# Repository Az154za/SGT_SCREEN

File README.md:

# SGT_SCREEN
Well this is a DEV BOARD that has 12*12 led screen ( matrix) driven by led DRIVER IS31FL3737 and controlled by RP2040
# SCHEMATIC

# PCB

# 3D preview 

# BOM
| # | Component | Supplier | Qty | Unit Price | Total (USD) |
|---|-----------|----------|-----|------------|-------------|
| 1 | PCB | JLCPCB | 2 | $81 | $81 |
| | | | | **TOTAL** | **$81** |

I hope you like this project

This project is sponsored by @JLCPCB

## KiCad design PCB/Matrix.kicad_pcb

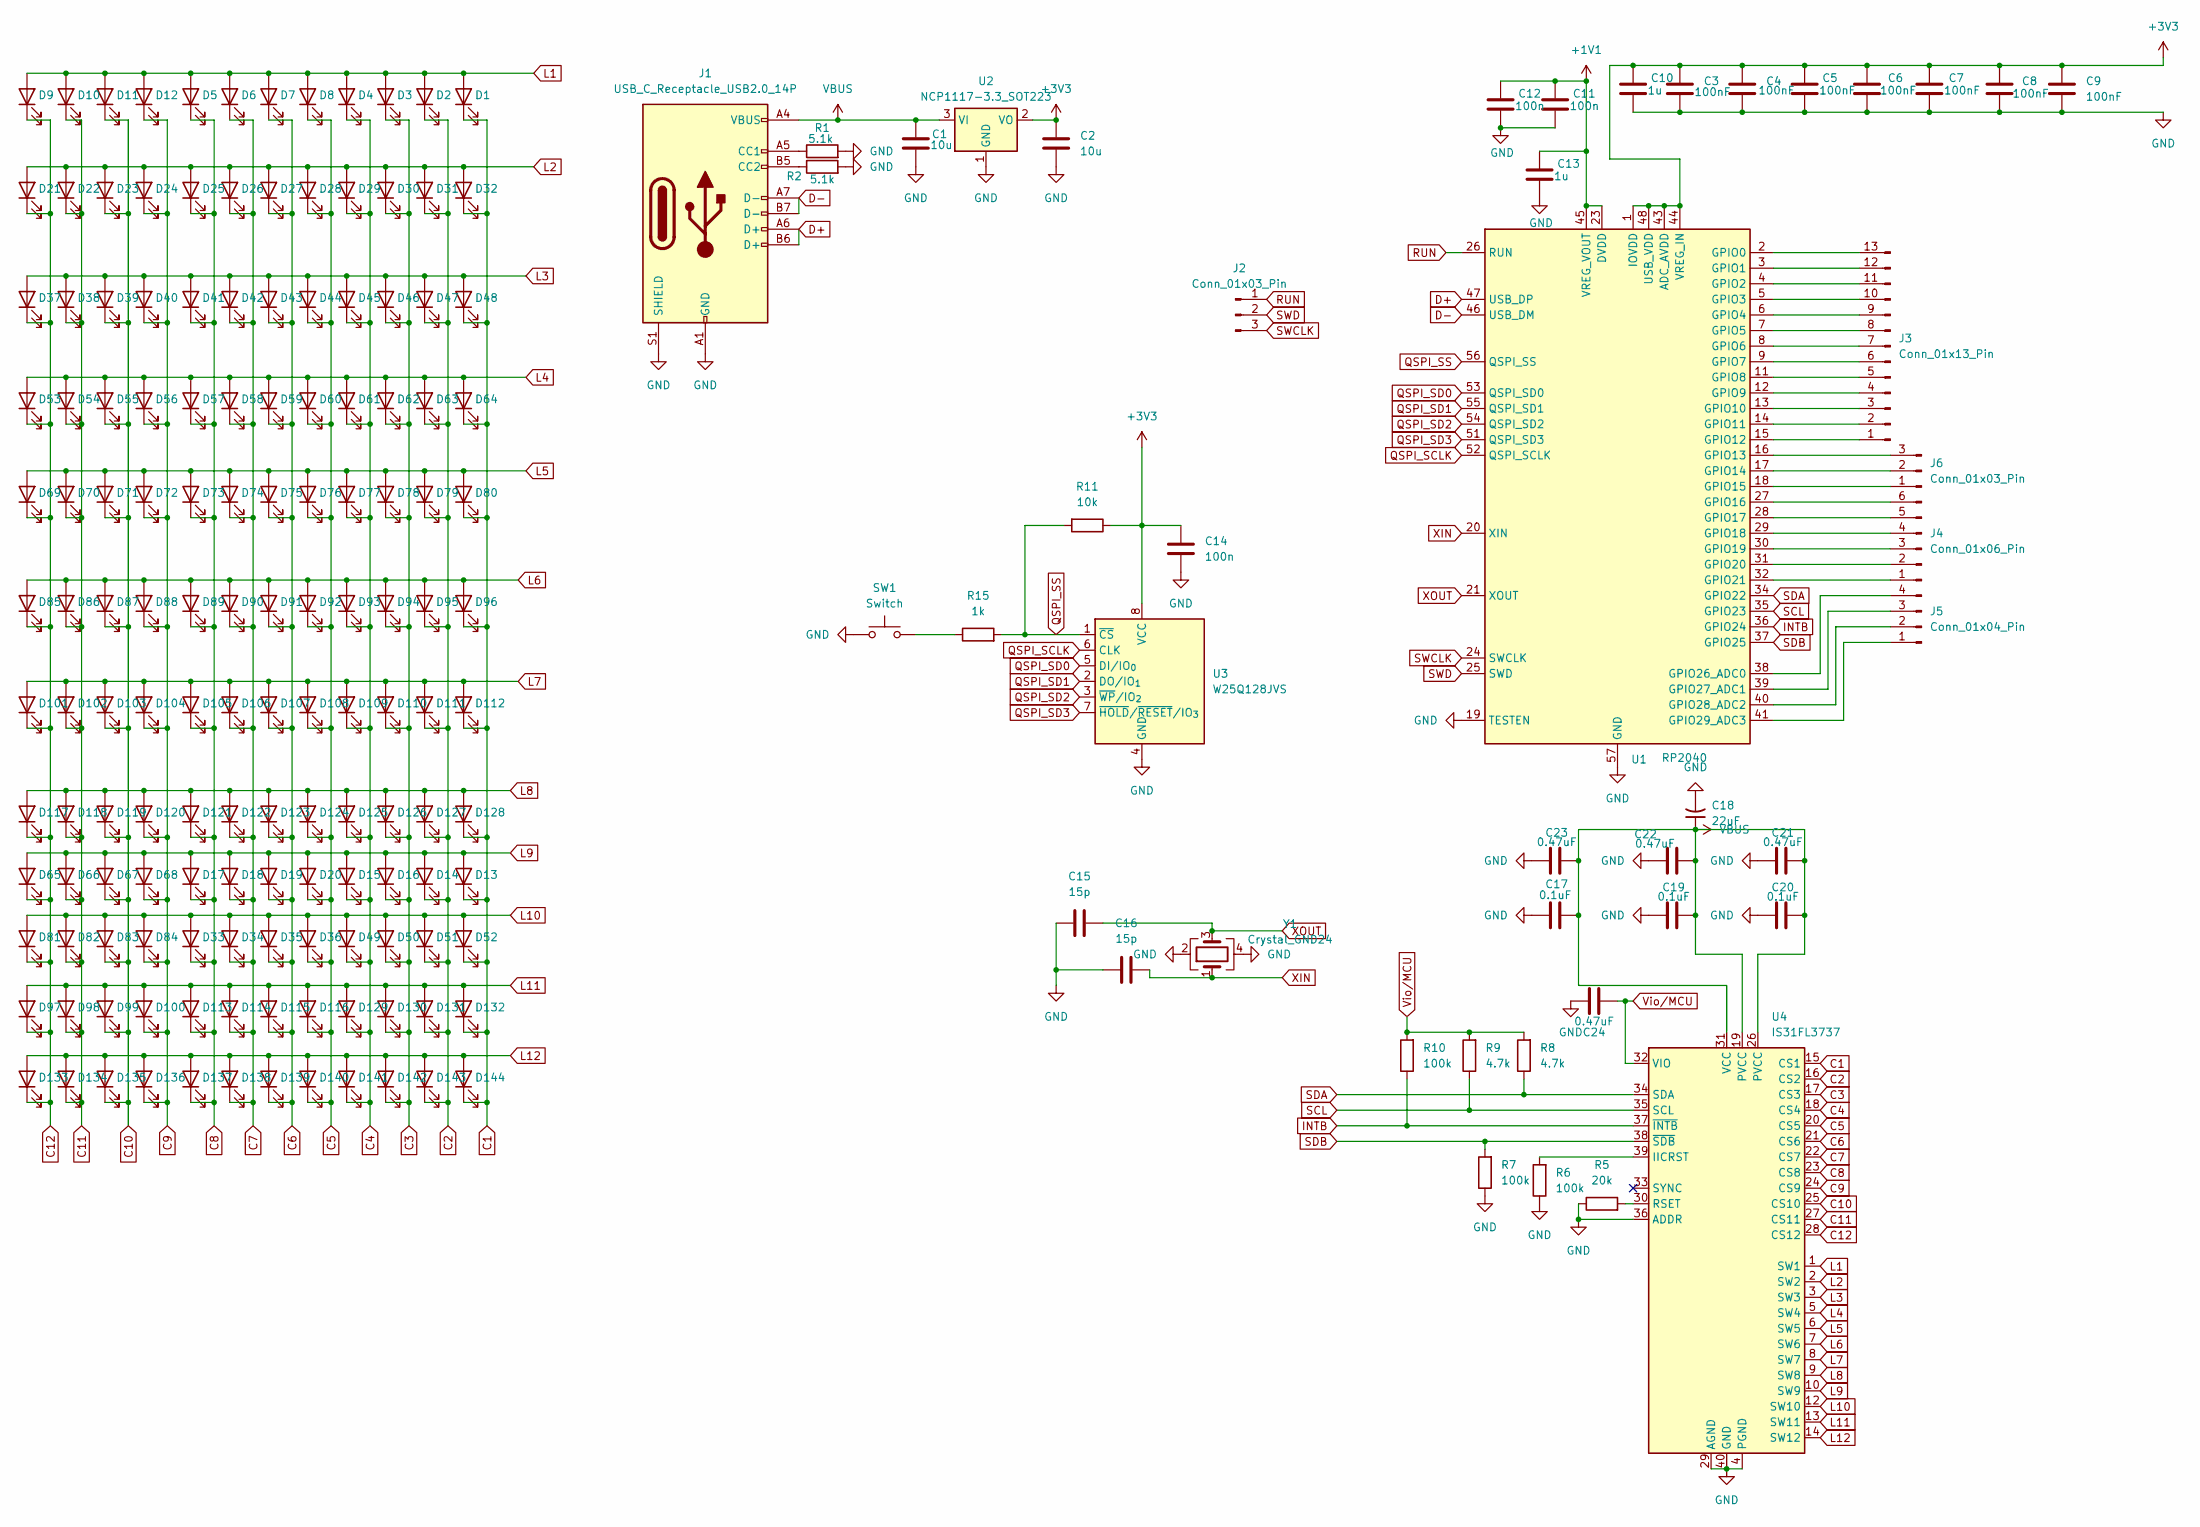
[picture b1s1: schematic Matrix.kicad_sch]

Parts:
C1, C2: 10u; C_0603_1608Metric
C3, C4, C5, C6, C7, C8, C9: 100nF; C_0402_1005Metric
C10, C13: 1u; C_0402_1005Metric
C11, C12, C14: 100n; C_0402_1005Metric
C15, C16: 15p; C_0402_1005Metric
C17, C19, C20: 0.1uF; C_0402_1005Metric
C18: 22uF; C_0402_1005Metric
C21, C22, C23, C24: 0.47uF; C_0402_1005Metric
D1, D2, D3, D4, D5, D6, D7, D8, D9, D10, D11, D12, D13, D14, D15, D16, D17, D18, D19, D20, D21, D22, D23, D24, D25, D26, D27, D28, D29, D30, D31, D32, D33, D34, D35, D36, D37, D38, D39, D40, D41, D42, D43, D44, D45, D46, D47, D48, D49, D50, D51, D52, D53, D54, D55, D56, D57, D58, D59, D60, D61, D62, D63, D64, D65, D66, D67, D68, D69, D70, D71, D72, D73, D74, D75, D76, D77, D78, D79, D80, D81, D82, D83, D84, D85, D86, D87, D88, D89, D90, D91, D92, D93, D94, D95, D96, D97, D98, D99, D100, D101, D102, D103, D104, D105, D106, D107, D108, D109, D110, D111, D112, D113, D114, D115, D116, D117, D118, D119, D120, D121, D122, D123, D124, D125, D126, D127, D128, D129, D130, D131, D132, D133, D134, D135, D136, D137, D138, D139, D140, D141, D142, D143, D144: LED; LED_0402_1005Metric
J1: USB_C_Receptacle_USB2.0_14P; USB_C_Receptacle_HRO_TYPE-C-31-M-12
J2: Conn_01x03_Pin; PinSocket_1x03_P2.54mm_Vertical
J3: Conn_01x13_Pin; PinHeader_1x13_P1.00mm_Vertical_SMD_Pin1Left
J4: Conn_01x06_Pin; PinHeader_1x06_P1.00mm_Vertical_SMD_Pin1Left
J5: Conn_01x04_Pin; PinHeader_1x04_P1.00mm_Vertical_SMD_Pin1Left
J6: Conn_01x03_Pin; PinHeader_1x03_P1.00mm_Vertical_SMD_Pin1Left
R1, R2: 5.1k; R_0402_1005Metric
R5: 20k; R_0402_1005Metric
R6, R7, R10: 100k; R_0402_1005Metric
R8, R9: 4.7k; R_0402_1005Metric
R11: 10k; R_0402_1005Metric
R15: 1k; R_0402_1005Metric
SW1: Switch; SW_SPST_SKQG_WithoutStem
U1: RP2040; QFN-56-1EP_7x7mm_P0.4mm_EP3.2x3.2mm
U2: NCP1117-3.3_SOT223; SOT-223-3_TabPin2
U3: W25Q128JVS; SOIC-8_5.3x5.3mm_P1.27mm
U4: IS31FL3737; QFN-40-1EP_5x5mm_P0.4mm_EP3.8x3.8mm
Y1: Crystal_GND24; Crystal_SMD_3225-4Pin_3.2x2.5mm

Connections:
+1V1: C11.1, C12.1, C13.1, U1.23 (DVDD), U1.45 (VREG_VOUT), U1.50 (DVDD)
+3V3: C2.1, C3.1, C4.1, C5.1, C6.1, C7.1, C8.1, C9.1, C10.1, C14.1, R11.1, U1.1 (IOVDD), U1.10 (IOVDD), U1.22 (IOVDD), U1.33 (IOVDD), U1.42 (IOVDD), U1.43 (ADC_AVDD), U1.44 (VREG_IN), U1.48 (USB_VDD), U1.49 (IOVDD), U2.2 (VO), U3.8 (VCC)
C1: D1.1 (K), D13.1 (K), D32.1 (K), D48.1 (K), D52.1 (K), D64.1 (K), D80.1 (K), D96.1 (K), D112.1 (K), D128.1 (K), D132.1 (K), D144.1 (K), U4.15 (CS1)
C2: D2.1 (K), D14.1 (K), D31.1 (K), D47.1 (K), D51.1 (K), D63.1 (K), D79.1 (K), D95.1 (K), D111.1 (K), D127.1 (K), D131.1 (K), D143.1 (K), U4.16 (CS2)
C3: D3.1 (K), D16.1 (K), D30.1 (K), D46.1 (K), D50.1 (K), D62.1 (K), D78.1 (K), D94.1 (K), D110.1 (K), D126.1 (K), D130.1 (K), D142.1 (K), U4.17 (CS3)
C4: D4.1 (K), D15.1 (K), D29.1 (K), D45.1 (K), D49.1 (K), D61.1 (K), D77.1 (K), D93.1 (K), D109.1 (K), D125.1 (K), D129.1 (K), D141.1 (K), U4.18 (CS4)
C5: D8.1 (K), D20.1 (K), D28.1 (K), D36.1 (K), D44.1 (K), D60.1 (K), D76.1 (K), D92.1 (K), D108.1 (K), D116.1 (K), D124.1 (K), D140.1 (K), U4.20 (CS5)
C6: D7.1 (K), D19.1 (K), D27.1 (K), D35.1 (K), D43.1 (K), D59.1 (K), D75.1 (K), D91.1 (K), D107.1 (K), D115.1 (K), D123.1 (K), D139.1 (K), U4.21 (CS6)
C7: D6.1 (K), D18.1 (K), D26.1 (K), D34.1 (K), D42.1 (K), D58.1 (K), D74.1 (K), D90.1 (K), D106.1 (K), D114.1 (K), D122.1 (K), D138.1 (K), U4.22 (CS7)
C8: D5.1 (K), D17.1 (K), D25.1 (K), D33.1 (K), D41.1 (K), D57.1 (K), D73.1 (K), D89.1 (K), D105.1 (K), D113.1 (K), D121.1 (K), D137.1 (K), U4.23 (CS8)
C9: D12.1 (K), D24.1 (K), D40.1 (K), D56.1 (K), D68.1 (K), D72.1 (K), D84.1 (K), D88.1 (K), D100.1 (K), D104.1 (K), D120.1 (K), D136.1 (K), U4.24 (CS9)
C10: D11.1 (K), D23.1 (K), D39.1 (K), D55.1 (K), D67.1 (K), D71.1 (K), D83.1 (K), D87.1 (K), D99.1 (K), D103.1 (K), D119.1 (K), D135.1 (K), U4.25 (CS10)
C11: D10.1 (K), D22.1 (K), D38.1 (K), D54.1 (K), D66.1 (K), D70.1 (K), D82.1 (K), D86.1 (K), D98.1 (K), D102.1 (K), D118.1 (K), D134.1 (K), U4.27 (CS11)
C12: D9.1 (K), D21.1 (K), D37.1 (K), D53.1 (K), D65.1 (K), D69.1 (K), D81.1 (K), D85.1 (K), D97.1 (K), D101.1 (K), D117.1 (K), D133.1 (K), U4.28 (CS12)
D+: J1.A6 (D+), J1.B6 (D+), U1.47 (USB_DP)
D-: J1.A7 (D-), J1.B7 (D-), U1.46 (USB_DM)
GND: C1.2, C2.2, C3.2, C4.2, C5.2, C6.2, C7.2, C8.2, C9.2, C10.2, C11.2, C12.2, C13.2, C14.2, C15.1, C16.1, C17.1, C18.2, C19.1, C20.1, C21.1, C22.1, C23.1, C24.2, J1.A1 (GND), J1.A12 (GND), J1.B1 (GND), J1.B12 (GND), J1.S1 (SHIELD), R1.2, R2.2, R5.1, R6.1, R7.1, SW1.1, U1.19 (TESTEN), U1.57 (GND), U2.1 (GND), U3.4 (GND), U4.4 (PGND), U4.11 (PGND), U4.29 (AGND), U4.36 (ADDR), U4.40 (GND), U4.41 (GND), Y1.2, Y1.4
INTB: R10.1, U1.36 (GPIO24), U4.37 (~INTB)
L1: D1.2 (A), D2.2 (A), D3.2 (A), D4.2 (A), D5.2 (A), D6.2 (A), D7.2 (A), D8.2 (A), D9.2 (A), D10.2 (A), D11.2 (A), D12.2 (A), U4.1 (SW1)
L2: D21.2 (A), D22.2 (A), D23.2 (A), D24.2 (A), D25.2 (A), D26.2 (A), D27.2 (A), D28.2 (A), D29.2 (A), D30.2 (A), D31.2 (A), D32.2 (A), U4.2 (SW2)
L3: D37.2 (A), D38.2 (A), D39.2 (A), D40.2 (A), D41.2 (A), D42.2 (A), D43.2 (A), D44.2 (A), D45.2 (A), D46.2 (A), D47.2 (A), D48.2 (A), U4.3 (SW3)
L4: D53.2 (A), D54.2 (A), D55.2 (A), D56.2 (A), D57.2 (A), D58.2 (A), D59.2 (A), D60.2 (A), D61.2 (A), D62.2 (A), D63.2 (A), D64.2 (A), U4.5 (SW4)
L5: D69.2 (A), D70.2 (A), D71.2 (A), D72.2 (A), D73.2 (A), D74.2 (A), D75.2 (A), D76.2 (A), D77.2 (A), D78.2 (A), D79.2 (A), D80.2 (A), U4.6 (SW5)
L6: D85.2 (A), D86.2 (A), D87.2 (A), D88.2 (A), D89.2 (A), D90.2 (A), D91.2 (A), D92.2 (A), D93.2 (A), D94.2 (A), D95.2 (A), D96.2 (A), U4.7 (SW6)
L7: D101.2 (A), D102.2 (A), D103.2 (A), D104.2 (A), D105.2 (A), D106.2 (A), D107.2 (A), D108.2 (A), D109.2 (A), D110.2 (A), D111.2 (A), D112.2 (A), U4.8 (SW7)
L8: D117.2 (A), D118.2 (A), D119.2 (A), D120.2 (A), D121.2 (A), D122.2 (A), D123.2 (A), D124.2 (A), D125.2 (A), D126.2 (A), D127.2 (A), D128.2 (A), U4.9 (SW8)
L9: D13.2 (A), D14.2 (A), D15.2 (A), D16.2 (A), D17.2 (A), D18.2 (A), D19.2 (A), D20.2 (A), D65.2 (A), D66.2 (A), D67.2 (A), D68.2 (A), U4.10 (SW9)
L10: D33.2 (A), D34.2 (A), D35.2 (A), D36.2 (A), D49.2 (A), D50.2 (A), D51.2 (A), D52.2 (A), D81.2 (A), D82.2 (A), D83.2 (A), D84.2 (A), U4.12 (SW10)
L11: D97.2 (A), D98.2 (A), D99.2 (A), D100.2 (A), D113.2 (A), D114.2 (A), D115.2 (A), D116.2 (A), D129.2 (A), D130.2 (A), D131.2 (A), D132.2 (A), U4.13 (SW11)
L12: D133.2 (A), D134.2 (A), D135.2 (A), D136.2 (A), D137.2 (A), D138.2 (A), D139.2 (A), D140.2 (A), D141.2 (A), D142.2 (A), D143.2 (A), D144.2 (A), U4.14 (SW12)
unnamed: J1.A5 (CC1), R1.1
unnamed: J1.B5 (CC2), R2.1
unnamed: J3.1, U1.15 (GPIO12)
unnamed: J3.2, U1.14 (GPIO11)
unnamed: J3.3, U1.13 (GPIO10)
unnamed: J3.4, U1.12 (GPIO9)
unnamed: J3.5, U1.11 (GPIO8)
unnamed: J3.6, U1.9 (GPIO7)
unnamed: J3.7, U1.8 (GPIO6)
unnamed: J3.8, U1.7 (GPIO5)
unnamed: J3.9, U1.6 (GPIO4)
unnamed: J3.10, U1.5 (GPIO3)
unnamed: J3.11, U1.4 (GPIO2)
unnamed: J3.12, U1.3 (GPIO1)
unnamed: J3.13, U1.2 (GPIO0)
unnamed: J4.1, U1.32 (GPIO21)
unnamed: J4.2, U1.31 (GPIO20)
unnamed: J4.3, U1.30 (GPIO19)
unnamed: J4.4, U1.29 (GPIO18)
unnamed: J4.5, U1.28 (GPIO17)
unnamed: J4.6, U1.27 (GPIO16)
unnamed: J5.1, U1.41 (GPIO29_ADC3)
unnamed: J5.2, U1.40 (GPIO28_ADC2)
unnamed: J5.3, U1.39 (GPIO27_ADC1)
unnamed: J5.4, U1.38 (GPIO26_ADC0)
unnamed: J6.1, U1.18 (GPIO15)
unnamed: J6.2, U1.17 (GPIO14)
unnamed: J6.3, U1.16 (GPIO13)
unnamed: R15.1, SW1.2
unnamed: R6.2, U4.39 (IICRST)
unnamed: R5.2, U4.30 (RSET)
QSPI_SCLK: U1.52 (QSPI_SCLK), U3.6 (CLK)
QSPI_SD0: U1.53 (QSPI_SD0), U3.5 (DI/IO_{0})
QSPI_SD1: U1.55 (QSPI_SD1), U3.2 (DO/IO_{1})
QSPI_SD2: U1.54 (QSPI_SD2), U3.3 (~WP/IO_{2})
QSPI_SD3: U1.51 (QSPI_SD3), U3.7 (~HOLD/~RESET/IO_{3})
QSPI_SS: R11.2, R15.2, U1.56 (QSPI_SS), U3.1 (~CS)
RUN: J2.1, U1.26 (RUN)
SCL: R9.1, U1.35 (GPIO23), U4.35 (SCL)
SDA: R8.1, U1.34 (GPIO22), U4.34 (SDA)
SDB: R7.2, U1.37 (GPIO25), U4.38 (~SDB)
SWCLK: J2.3, U1.24 (SWCLK)
SWD: J2.2, U1.25 (SWD)
VBUS: C1.1, C17.2, C18.1, C19.2, C20.2, C21.2, C22.2, C23.2, J1.A4 (VBUS), J1.A9 (VBUS), J1.B4 (VBUS), J1.B9 (VBUS), U2.3 (VI), U4.19 (PVCC), U4.26 (PVCC), U4.31 (VCC)
Vio/MCU: C24.1, R8.2, R9.2, R10.2, U4.32 (VIO)
XIN: C16.2, U1.20 (XIN), Y1.1
XOUT: C15.2, U1.21 (XOUT), Y1.3

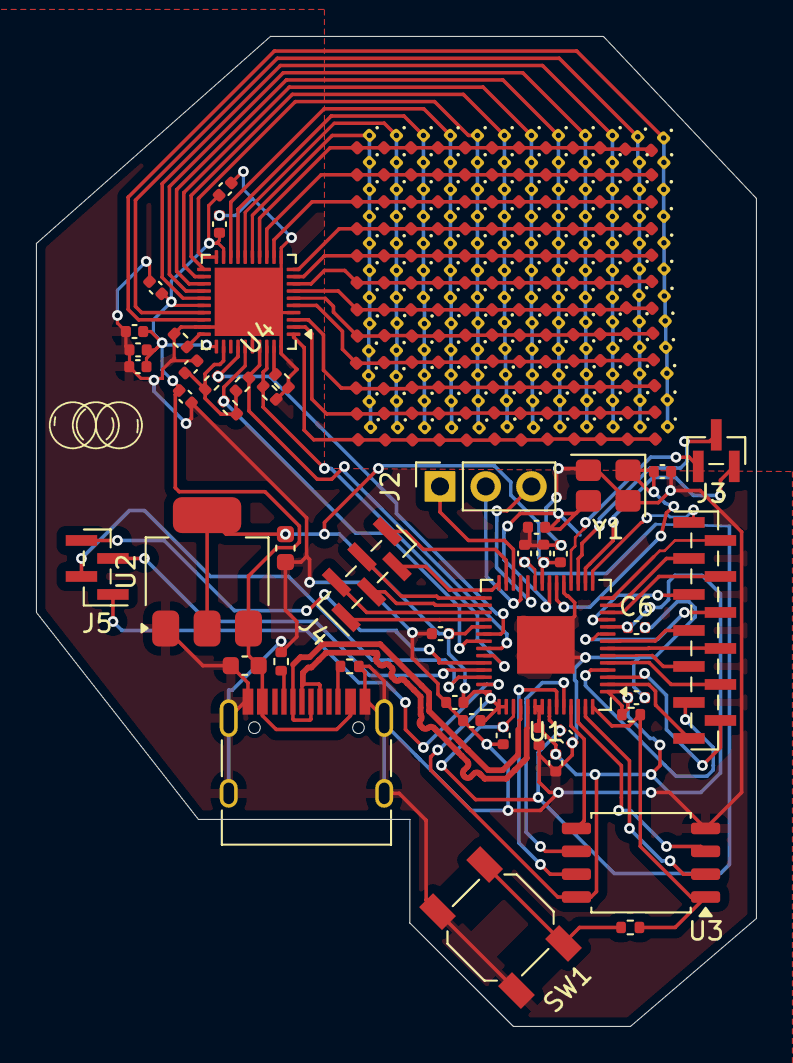
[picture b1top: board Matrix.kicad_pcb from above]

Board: 2 copper layers, 40.0 x 55.0 mm, 190 parts (0 on the bottom side), 77 nets.

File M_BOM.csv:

Designator,Footprint,Quantity,Value,LCSC Part #
C1,0603,1,10uF,C19702
C2,0603,1,10uF,C19702
C10,0402,1,1uF,C52923
C13,0402,1,1uF,C52923
C11,0402,1,100nF,C1525
C12,0402,1,100nF,C1525
C14,0402,1,100nF,C1525
C15,0402,1,15pF,C1548
C16,0402,1,15pF,C1548
C17,0402,1,0.1uF,C1525
C19,0402,1,0.1uF,C1525
C20,0402,1,0.1uF,C1525
C18,0805,1,22uF,C15850
C21,0402,1,0.47uF,C105883
C22,0402,1,0.47uF,C105883
C23,0402,1,0.47uF,C105883
C24,0402,1,0.47uF,C105883
C3,0402,1,100nF,C1525
C4,0402,1,100nF,C1525
C5,0402,1,100nF,C1525
C6,0402,1,100nF,C1525
C7,0402,1,100nF,C1525
C8,0402,1,100nF,C1525
C9,0402,1,100nF,C1525
D1,0603,1,LED,C2286
D2,0603,1,LED,C2286
D3,0603,1,LED,C2286
D4,0603,1,LED,C2286
D5,0603,1,LED,C2286
D6,0603,1,LED,C2286
D7,0603,1,LED,C2286
D8,0603,1,LED,C2286
D9,0603,1,LED,C2286
D10,0603,1,LED,C2286
D11,0603,1,LED,C2286
D12,0603,1,LED,C2286
D13,0603,1,LED,C2286
D14,0603,1,LED,C2286
D15,0603,1,LED,C2286
D16,0603,1,LED,C2286
D17,0603,1,LED,C2286
D18,0603,1,LED,C2286
D19,0603,1,LED,C2286
D20,0603,1,LED,C2286
D21,0603,1,LED,C2286
D22,0603,1,LED,C2286
D23,0603,1,LED,C2286
D24,0603,1,LED,C2286
D25,0603,1,LED,C2286
D26,0603,1,LED,C2286
D27,0603,1,LED,C2286
D28,0603,1,LED,C2286
D29,0603,1,LED,C2286
D30,0603,1,LED,C2286
D31,0603,1,LED,C2286
D32,0603,1,LED,C2286
D33,0603,1,LED,C2286
D34,0603,1,LED,C2286
D35,0603,1,LED,C2286
D36,0603,1,LED,C2286
D37,0603,1,LED,C2286
D38,0603,1,LED,C2286
D39,0603,1,LED,C2286
D40,0603,1,LED,C2286
D41,0603,1,LED,C2286
D42,0603,1,LED,C2286
D43,0603,1,LED,C2286
D44,0603,1,LED,C2286
D45,0603,1,LED,C2286
D46,0603,1,LED,C2286
D47,0603,1,LED,C2286
D48,0603,1,LED,C2286
D49,0603,1,LED,C2286
D50,0603,1,LED,C2286
D51,0603,1,LED,C2286
D52,0603,1,LED,C2286
D53,0603,1,LED,C2286
D54,0603,1,LED,C2286
D55,0603,1,LED,C2286
D56,0603,1,LED,C2286
D57,0603,1,LED,C2286
D58,0603,1,LED,C2286
D59,0603,1,LED,C2286
D60,0603,1,LED,C2286
D61,0603,1,LED,C2286
D62,0603,1,LED,C2286
D63,0603,1,LED,C2286
D64,0603,1,LED,C2286
D65,0603,1,LED,C2286
D66,0603,1,LED,C2286
D67,0603,1,LED,C2286
D68,0603,1,LED,C2286
D69,0603,1,LED,C2286
D70,0603,1,LED,C2286
D71,0603,1,LED,C2286
D72,0603,1,LED,C2286
D73,0603,1,LED,C2286
D74,0603,1,LED,C2286
D75,0603,1,LED,C2286
D76,0603,1,LED,C2286
D77,0603,1,LED,C2286
D78,0603,1,LED,C2286
D79,0603,1,LED,C2286
D80,0603,1,LED,C2286
D81,0603,1,LED,C2286
D82,0603,1,LED,C2286
D83,0603,1,LED,C2286
D84,0603,1,LED,C2286
D85,0603,1,LED,C2286
D86,0603,1,LED,C2286
D87,0603,1,LED,C2286
D88,0603,1,LED,C2286
D89,0603,1,LED,C2286
D90,0603,1,LED,C2286
D91,0603,1,LED,C2286
D92,0603,1,LED,C2286
D93,0603,1,LED,C2286
D94,0603,1,LED,C2286
D95,0603,1,LED,C2286
D96,0603,1,LED,C2286
D97,0603,1,LED,C2286
D98,0603,1,LED,C2286
D99,0603,1,LED,C2286
D100,0603,1,LED,C2286
D101,0603,1,LED,C2286
D102,0603,1,LED,C2286
D103,0603,1,LED,C2286
D104,0603,1,LED,C2286
D105,0603,1,LED,C2286
D106,0603,1,LED,C2286
D107,0603,1,LED,C2286
D108,0603,1,LED,C2286
D109,0603,1,LED,C2286
D110,0603,1,LED,C2286
D111,0603,1,LED,C2286
D112,0603,1,LED,C2286
D113,0603,1,LED,C2286
D114,0603,1,LED,C2286
D115,0603,1,LED,C2286
D116,0603,1,LED,C2286
D117,0603,1,LED,C2286
D118,0603,1,LED,C2286
D119,0603,1,LED,C2286
D120,0603,1,LED,C2286
D121,0603,1,LED,C2286
D122,0603,1,LED,C2286
D123,0603,1,LED,C2286
D124,0603,1,LED,C2286
D125,0603,1,LED,C2286
D126,0603,1,LED,C2286
D127,0603,1,LED,C2286
D128,0603,1,LED,C2286
D129,0603,1,LED,C2286
D130,0603,1,LED,C2286
D131,0603,1,LED,C2286
D132,0603,1,LED,C2286
D133,0603,1,LED,C2286
D134,0603,1,LED,C2286
D135,0603,1,LED,C2286
D136,0603,1,LED,C2286
D137,0603,1,LED,C2286
D138,0603,1,LED,C2286
D139,0603,1,LED,C2286
D140,0603,1,LED,C2286
D141,0603,1,LED,C2286
D142,0603,1,LED,C2286
D143,0603,1,LED,C2286
D144,0603,1,LED,C2286
J1,USB_C_Receptacle_HRO_TYPE-C-31-M-12,1,USB_C_Receptacle_USB2.0_14P,C165948
J2,PinSocket_1x03_P2.54mm_Vertical,1,Conn_01x03_Pin,
J3,PinHeader_2x06_P2.54mm_Vertical,1,Conn_01x11_Pin,
J4,PinHeader_2x06_P2.54mm_Vertical,1,Conn_01x11_Pin,
J6,PinHeader_1x04_P2.54mm_Vertical,1,Conn_01x04_Socket,
R1,0402,1,5.1k,C25905
R2,0402,1,5.1k,C25905
R10,0402,1,100k,C25741
R6,0402,1,100k,C25741
R7,0402,1,100k,C25741
R15,0402,1,1k,C11702
R3,0402,1,27.4,C25100
R4,0402,1,27.4,C25100
R5,0402,1,20k,C25765
R8,0402,1,4.7k,C25900
R9,0402,1,4.7k,C25900
SW1,SW_SPST_SKQG_WithoutStem,1,Switch,C318884
U1,QFN-56-1EP_7x7mm_P0.4mm_EP3.2x3.2mm,1,RP2040,C2040
U2,SOT-223-3_TabPin2,1,NCP1117-3.3_SOT223,C6186
U3,SOIC-8_5.3x5.3mm_P1.27mm,1,W25Q128JVS,C97521
U4,QFN-40-1EP_5x5mm_P0.4mm_EP3.8x3.8mm,1,IS31FL3737,C506254
Y1,Crystal_SMD_3225-4Pin_3.2x2.5mm,1,Crystal_GND24,C9002

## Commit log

2026-02-02 Update README with project details and images
    Added project description, schematic, PCB, and 3D preview images to README.
2026-03-01 Add BOM section to README
2026-03-26 Update 3D preview image in README
2026-04-30 Add sponsorship mention in README
